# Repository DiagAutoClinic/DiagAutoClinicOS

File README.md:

<!-- HEADER -->

<h1 align="center">DiagAuto Suite</h1>
<h3 align="center">Intelligent CAN Diagnostics &amp; Analysis Platform</h3>

<p align="center">
  <strong>Focused • Hardware-Agnostic • Workshop-Grade</strong><br/>
  Built to analyze, understand, and validate vehicle CAN systems with precision.
</p>

---

# Sponsors / Support (most important)

**DiagAutoClinicOS is currently self-funded by the maintainer (Shaun Smit) and is actively seeking sponsors.**

If this project saves you time or helps your workshop, please consider supporting its development.

> **Support via PayPal → https://paypal.me/diagautoclinic**

Funding options are also listed in `.github/FUNDING.yml`.

---

## Hardware Validation

**Validated on:**
- Godiag GD101 J2534 device
- 500kbps CAN timing with microsecond precision
- ISO-TP fragmentation (FF/CF/FC with BS/STmin)
- Sub-100ms security access (0x27 service)
- USB hotplug recovery with auto-reconnect
- Concurrent session isolation (8 sessions)

**Test vehicles:** Pre-2010 vehicles (per safety protocol)

---

## In-Kind Support / Thanks

The following organizations have provided hardware or resources used during development and testing.

| Contributor                             | Contribution                                                                |
| --------------------------------------- | --------------------------------------------------------------------------- |
| **EshuTech Computers**                  | Development laptop (Acer TravelMate G2 Core i7) for DACOS build environment |
| **GoDiag** — https://godiag.com         | GT100 Plus GPT device for ECU and protocol testing                          |
| **ScanTool.net** — https://scantool.net | OBDLink MX+ adapters for compatibility and reliability testing              |

> In-kind support means hardware or resources were made available to assist development.
> It does **not** imply ongoing financial sponsorship or external funding.

---

## Sponsor Policy / Transparency

Sponsor relationships remain transparent and auditable.

- Sponsor support must never override safety boundaries, Restricted Mode policy, or verification gates.
- Sponsor influence over security controls is **not permitted**.
- Security mechanisms remain **fail-closed**.
- Sponsor-provided code or artifacts must be reviewable and testable.
- Sponsor acknowledgements remain visible in this repository.

---

# Overview

**DiagAuto Suite** is the first production component of **DiagAutoClinicOS (DACOS)**.

The current release focuses exclusively on:

- **CAN diagnostics**
- **signal analysis**
- **vehicle communication logging**

ECU flashing, immobilizer operations, and security access tooling are **intentionally excluded** from the AutoDiag alpha scope and are planned separately in the long-term roadmap.

This design choice prioritizes **stability, safety, and workshop reliability**.

---

## Versioning

This repository contains multiple components with different maturity levels.

- **AutoDiag**: diagnostics module (alpha readiness target: `v0.1`)
- **AutoECU**: programming module (alpha readiness target: `v0.1`, safety-gated)
- **AutoKey**: security/IMMO module (planned)

`config.py` currently sets the runtime/build version (example):

```python
APP_VERSION = "3.2.0"
```

---

## Statement

> "My software will fight you harder to not brick an ECU than most tools fight to stop piracy."
> — Shaun Smit

---

# Repository Layout

This tree is kept in sync with the repository root.

```text
DiagAutoClinicOS/
├── .github/                 GitHub configuration (CI, funding, templates)
├── AutoDiag/                CAN diagnostics suite (PyQt6)
├── AutoECU/                 ECU programming module (alpha / safety-gated)
├── AutoKey/                 Key / immobilizer module (planned)
├── assets/                  Images and static assets
├── core/                    Core shared logic
├── data/                    Reference datasets
├── docs/                    Documentation
├── drivers/                 Hardware driver abstraction / J2534 DLL drop-in
├── installers/              Windows installer scripts
├── layout_samples/          UI prototypes / layout concepts
├── live_tests/              Hardware test scripts
├── plans/                   Architecture plans
├── pulls/                   PR planning notes
├── resources/               Application resources
├── scripts/                 Utility scripts
├── shared/                  Shared modules
├── tests/                   Automated tests
├── ui/                      UI components (shared)
├── utils/                   General utilities
├── Windows Test/            Windows-specific testing
├── check_theme.py           Theme verification helper
├── check_vci.py             VCI verification helper
├── config.py                Global configuration
├── dtc_faults_dataset.json  DTC dataset
├── launcher.py              Suite launcher (PyQt6)
├── launch_autodiag.bat      Convenience launcher for AutoDiag
├── requirements.txt         Runtime dependencies
├── requirements-dev.txt     Development dependencies
├── requirements_32bit.txt   32-bit dependency set
├── pytest.ini               Test configuration
└── version_info.txt         Version info
```

---

# Installation

## System Requirements

- Windows 10 / 11 (64-bit)
- Python 3.10+
- Administrator privileges for hardware drivers

## Running from Source

```bash
git clone https://github.com/DiagAutoClinic/DiagAutoClinicOS.git
cd DiagAutoClinicOS
python -m venv venv
venv\\Scripts\\activate
pip install -r requirements.txt
python launcher.py
```

---

# License

This project is licensed under the **GNU General Public License v3.0**.

---

# Author

**Shaun Smit**  
Founder & Lead Engineer — DiagAutoClinic  
[shaun@diagautoclinic.co.za](mailto:shaun@diagautoclinic.co.za)

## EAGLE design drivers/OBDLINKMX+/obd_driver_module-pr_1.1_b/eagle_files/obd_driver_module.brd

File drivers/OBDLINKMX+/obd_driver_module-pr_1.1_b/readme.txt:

*********************************************************************
   OBD Driver Module, Rev 1.1/B
   Copyright (C) 2013 OBD Solutions, All Rights Reserved
*********************************************************************

======================================
============== Contents ==============
======================================

   eagle_files			Contains the EAGLE source files
   assy.gbr			Top assembly drawing (Gerber RS-274X)
   bom.xls			Bill of materials
   mount.mnt			SMD centroid file (XYRS)
   obd_driver_module.pdf	PDF of the schematic
   pcb.zip			Main PCB production files
   readme.txt			This file

======================================
=============== Notes ================
======================================

 - The gerber files provided are viewed from the top side.
 - Hole sizes are the finished hole sizes.
 - Excellon Format: 1.4 Leading, Absolute, Imperial
 - The board should be routed to the outline in fab.gbr

======================================
========= Revision History ===========
======================================

Rev 1.0	- David D (2012.10.27)
	  Initial release

Rev 1.1 - Jason (2013.09.17)
	  Connected all VOUT pins of regulator,reversed ISO comparator inputs
	  Updated PCB Rev to B

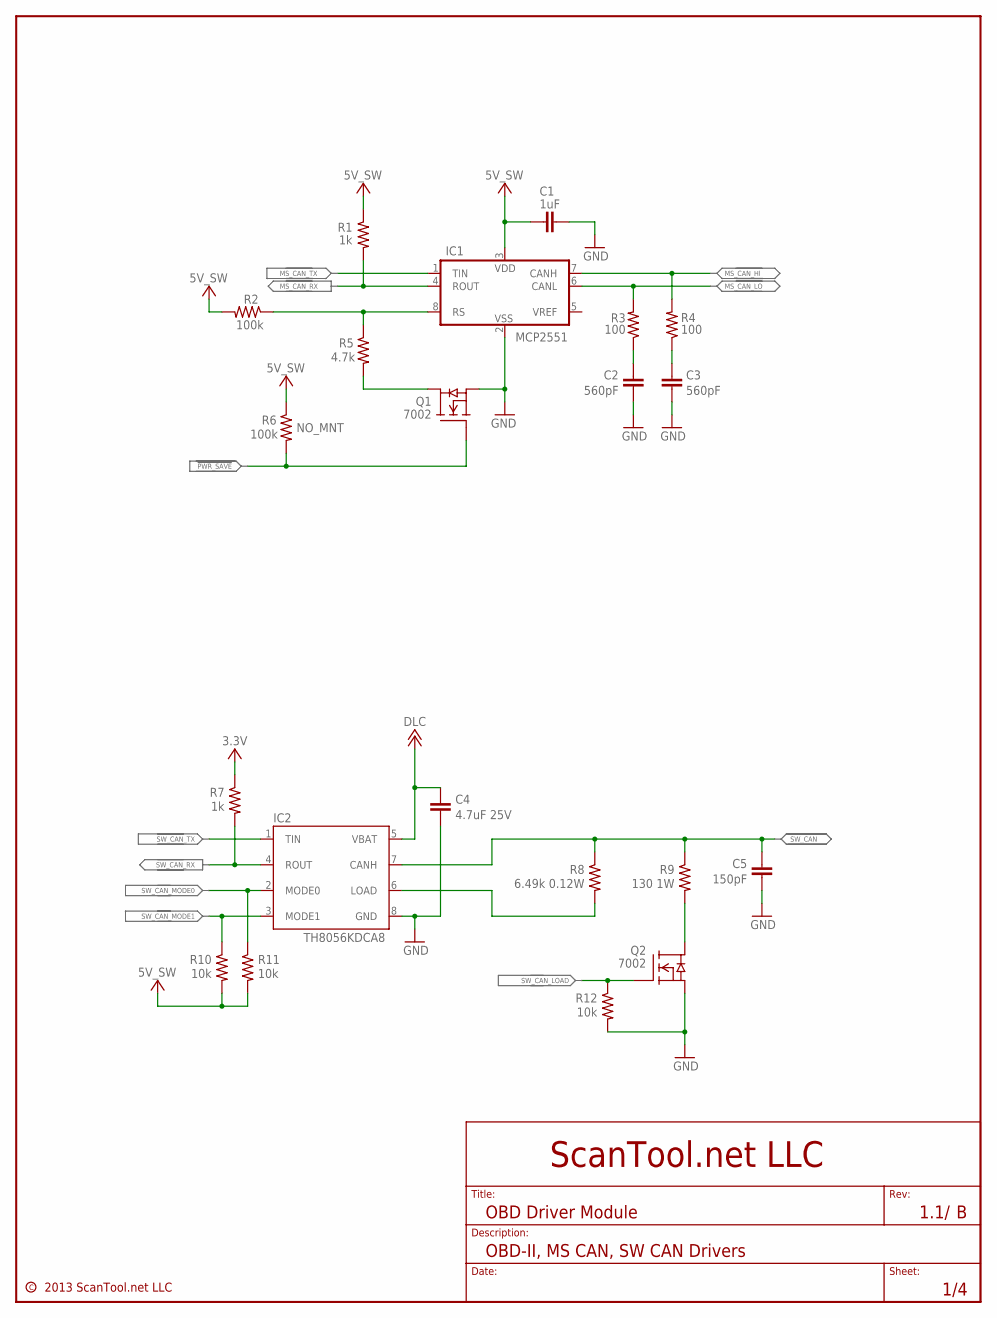
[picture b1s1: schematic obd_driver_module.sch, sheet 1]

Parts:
C1: 1uF; 0603
C2, C3: 560pF; 0603
C4: 4.7uF 25V; 0805
C5: 150pF; 0603
IC1: MCP2551; SO-8
IC2: TH8056KDCA8; SO-8
Q1, Q2: 7002; SOT323-3; PARTNUM 2N7002WT1G
R1, R7: 1k; 0603
R2, R6: 100k; 0603
R3, R4: 100; 0603
R5: 4.7k; 0603
R8: 6.49k 0.12W; 0603
R9: 130 1W; 2512
R10, R11, R12: 10k; 0603

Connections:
3.3V: R7.1; also elsewhere on the board
5V_SW: C1.1, IC1.3 (VDD), R1.1, R2.2, R6.1, R10.2, R11.2; also elsewhere on the board
!PWR_SAVE: Q1.1 (G), R6.2; also elsewhere on the board
DLC: C4.2, IC2.5 (VBAT); also elsewhere on the board
GND: C1.2, C2.2, C3.2, C4.1, C5.1, IC1.2 (VSS), IC2.8 (GND), Q1.2 (S), Q2.2 (S), R12.2; also elsewhere on the board
MS_CAN_HI: IC1.7 (CANH), R4.2; also elsewhere on the board
MS_CAN_LO: IC1.6 (CANL), R3.2; also elsewhere on the board
MS_CAN_RX: IC1.4 (ROUT), R1.2; also elsewhere on the board
MS_CAN_TX: IC1.1 (TIN); also elsewhere on the board
unnamed: C2.1, R3.1
unnamed: C3.1, R4.1
unnamed: IC1.8 (RS), R2.1, R5.1
unnamed: Q1.3 (D), R5.2
unnamed: IC2.6 (LOAD), R8.2
unnamed: Q2.3 (D), R9.P$2 (2)
SW_CAN: C5.2, IC2.7 (CANH), R8.1, R9.P$1 (1); also elsewhere on the board
SW_CAN_LOAD: Q2.1 (G), R12.1; also elsewhere on the board
SW_CAN_MODE0: IC2.2 (MODE0), R11.1; also elsewhere on the board
SW_CAN_MODE1: IC2.3 (MODE1), R10.1; also elsewhere on the board
SW_CAN_RX: IC2.4 (ROUT), R7.2; also elsewhere on the board
SW_CAN_TX: IC2.1 (TIN); also elsewhere on the board

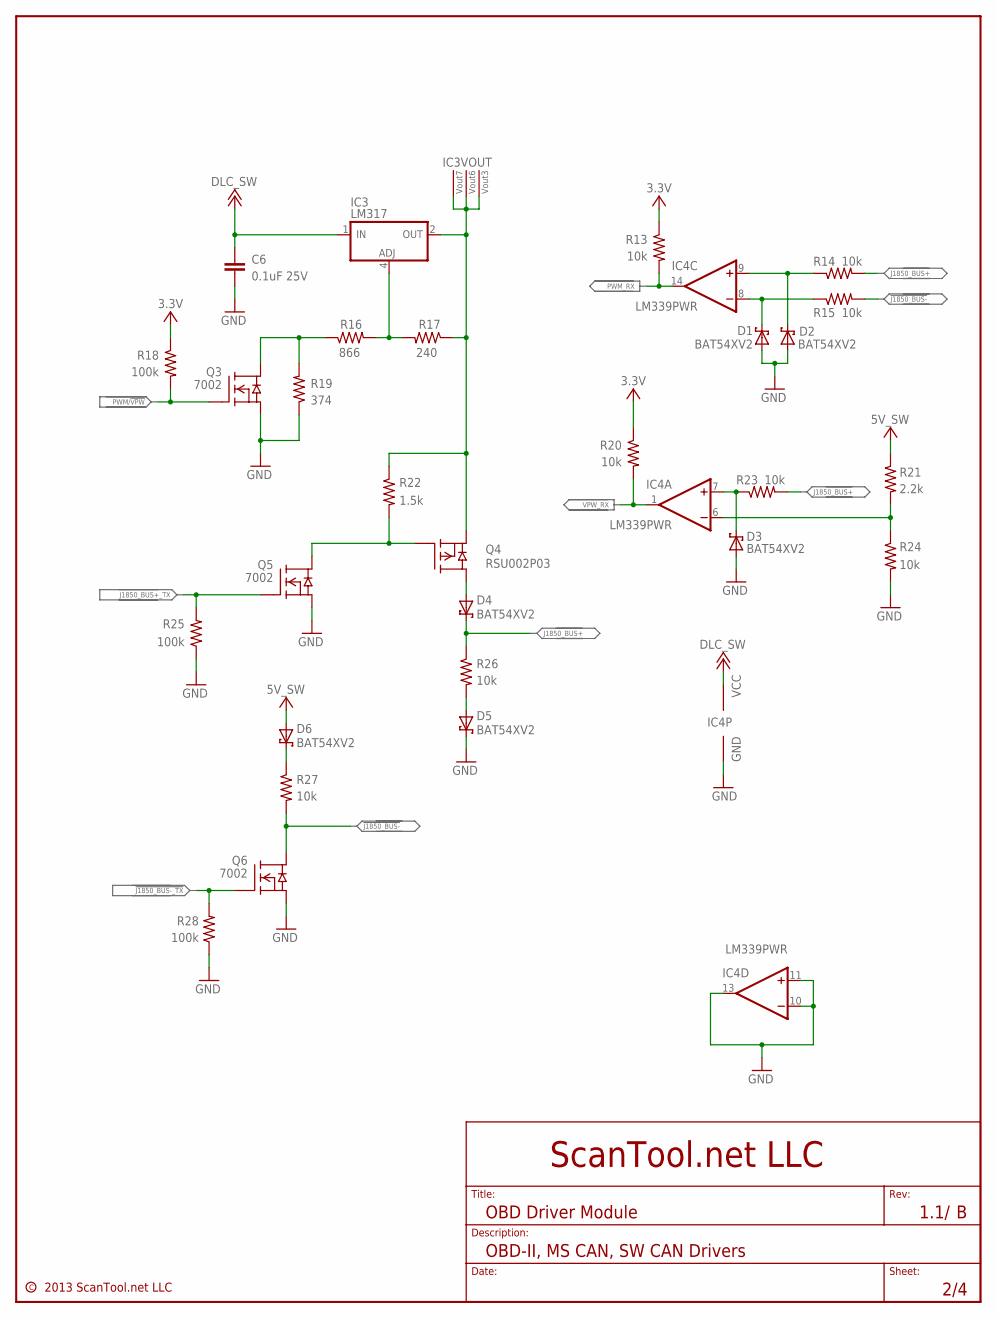
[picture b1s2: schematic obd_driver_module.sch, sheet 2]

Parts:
C6: 0.1uF 25V; 0603
D1, D2, D3: BAT54XV2; SOD-523F; PARTNUM BAT54XV2
D4, D5, D6: BAT54XV2; SOD-523F
IC3: LM317; TSSOP-8
IC4: LM339PWR; TSSOP-14
Q3, Q5, Q6: 7002; SOT323-3; PARTNUM 2N7002WT1G
Q4: RSU002P03; SOT323-3
R13, R14, R15, R20, R23, R24, R26, R27: 10k; 0603
R16: 866; 0603
R17: 240; 0603
R18, R25, R28: 100k; 0603
R19: 374; 0603
R21: 2.2k; 0603
R22: 1.5k; 0603

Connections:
3.3V: R13.1, R18.1, R20.1; also elsewhere on the board
5V_SW: D6.A, R21.1; also elsewhere on the board
!J1850_BUS-: Q6.3 (D), R15.2, R27.2; also elsewhere on the board
!J1850_BUS-_TX: Q6.1 (G), R28.2; also elsewhere on the board
DLC_SW: C6.1, IC3.1 (IN), IC4.3 (VCC); also elsewhere on the board
GND: C6.2, D1.A, D2.A, D3.A, D5.C, IC4.10 (-IN), IC4.11 (+IN), IC4.12 (GND), IC4.13 (OUT), Q3.2 (S), Q5.2 (S), Q6.2 (S), R19.1, R24.2, R25.1, R28.1; also elsewhere on the board
J1850_BUS+: D4.C, R14.2, R23.2, R26.1; also elsewhere on the board
J1850_BUS+_TX: Q5.1 (G), R25.2; also elsewhere on the board
unnamed: D6.C, R27.1
unnamed: Q4.1 (G), Q5.3 (D), R22.2
unnamed: Q3.3 (D), R16.1, R19.2
unnamed: D3.C, IC4.7 (+IN), R23.1
unnamed: D5.A, R26.2
unnamed: IC3.4 (ADJ), R16.2, R17.2
unnamed: D4.A, Q4.3 (D)
unnamed: D2.C, IC4.9 (+IN), R14.1
unnamed: D1.C, IC4.8 (-IN), R15.1
unnamed: IC4.6 (-IN), R21.2, R24.1
OUT: IC3.2 (OUT), IC3.3 (OUT), IC3.6 (OUT), IC3.7 (OUT), Q4.2 (S), R17.1, R22.1
PWM/!VPW: Q3.1 (G), R18.2; also elsewhere on the board
PWM_RX: IC4.14 (OUT), R13.2; also elsewhere on the board
VPW_RX: IC4.1 (OUT), R20.2; also elsewhere on the board

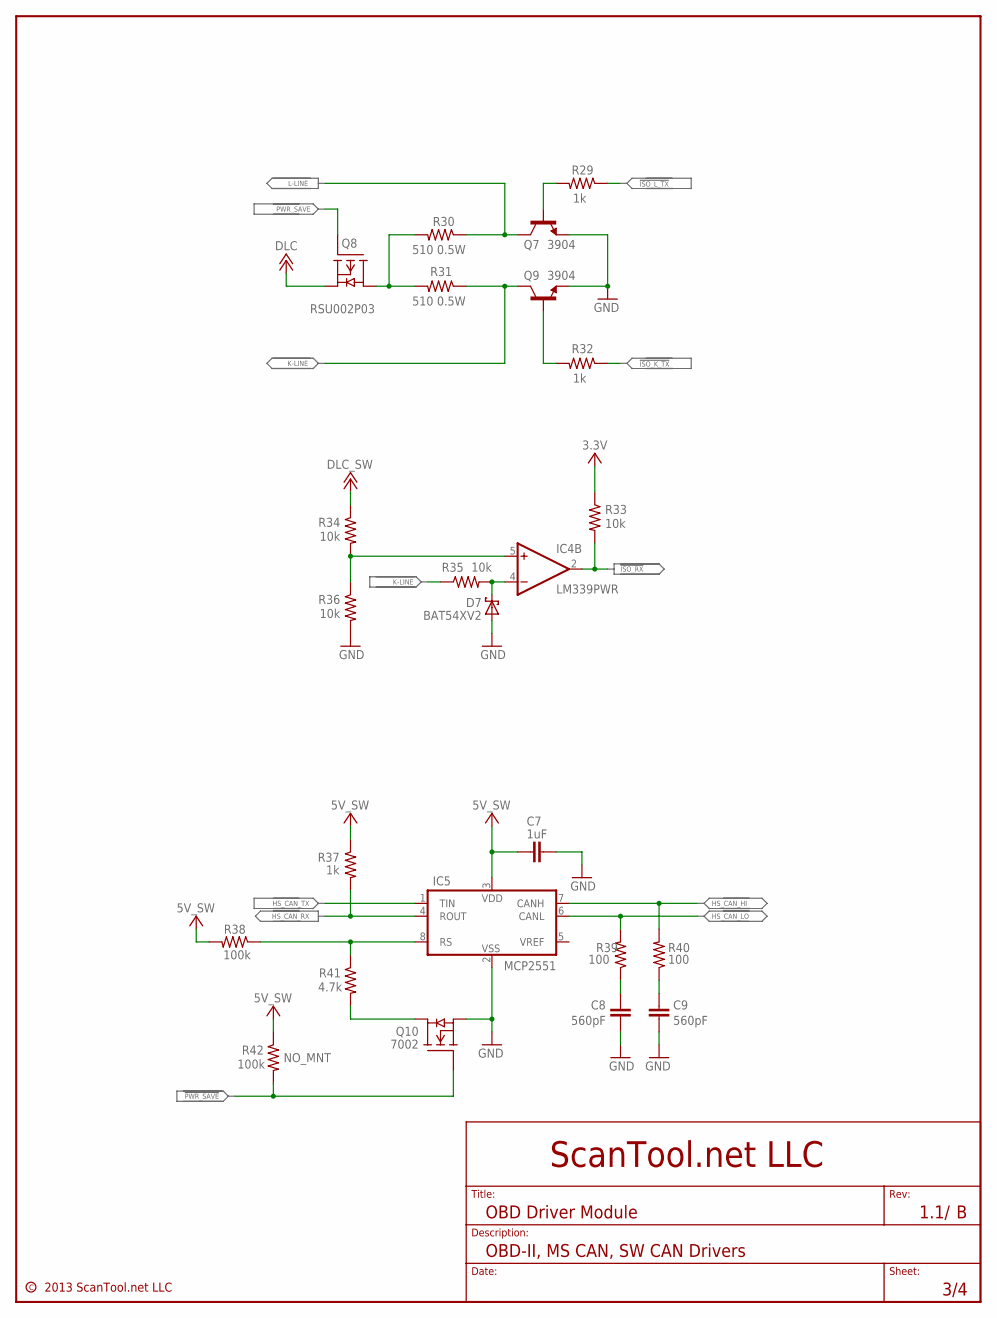
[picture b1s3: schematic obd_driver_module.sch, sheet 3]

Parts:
C7: 1uF; 0603
C8, C9: 560pF; 0603
D7: BAT54XV2; SOD-523F
IC4: LM339PWR; TSSOP-14
IC5: MCP2551; SO-8
Q7, Q9: 3904; SOT323-3
Q8: RSU002P03; SOT323-3
Q10: 7002; SOT323-3; PARTNUM 2N7002WT1G
R29, R32, R37: 1k; 0603
R30, R31: 510 0.5W; 1210
R33, R34, R35, R36: 10k; 0603
R38, R42: 100k; 0603
R39, R40: 100; 0603
R41: 4.7k; 0603

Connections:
3.3V: R33.1; also elsewhere on the board
5V_SW: C7.1, IC5.3 (VDD), R37.1, R38.2, R42.1; also elsewhere on the board
!ISO_K_TX: R32.1; also elsewhere on the board
!ISO_L_TX: R29.1; also elsewhere on the board
!ISO_RX: IC4.2 (OUT), R33.2; also elsewhere on the board
!PWR_SAVE: Q10.1 (G), R42.2; also elsewhere on the board
DLC: Q8.2 (S); also elsewhere on the board
DLC_SW: R34.1; also elsewhere on the board
GND: C7.2, C8.2, C9.2, D7.A, IC5.2 (VSS), Q7.2 (E), Q9.2 (E), Q10.2 (S), R36.2; also elsewhere on the board
HS_CAN_HI: IC5.7 (CANH), R40.2; also elsewhere on the board
HS_CAN_LO: IC5.6 (CANL), R39.2; also elsewhere on the board
HS_CAN_RX: IC5.4 (ROUT), R37.2; also elsewhere on the board
HS_CAN_TX: IC5.1 (TIN); also elsewhere on the board
K-LINE: Q9.3 (C), R31.1, R35.1; also elsewhere on the board
L-LINE: Q7.3 (C), R30.1; also elsewhere on the board
unnamed: C8.1, R39.1
unnamed: Q10.3 (D), R41.2
unnamed: Q7.1 (B), R29.2
unnamed: Q8.3 (D), R30.2, R31.2
unnamed: Q9.1 (B), R32.2
unnamed: D7.C, IC4.4 (-IN), R35.2
unnamed: IC5.8 (RS), R38.1, R41.1
unnamed: IC4.5 (+IN), R34.2, R36.1
unnamed: C9.1, R40.1
PWR_SAVE: Q8.1 (G); also elsewhere on the board

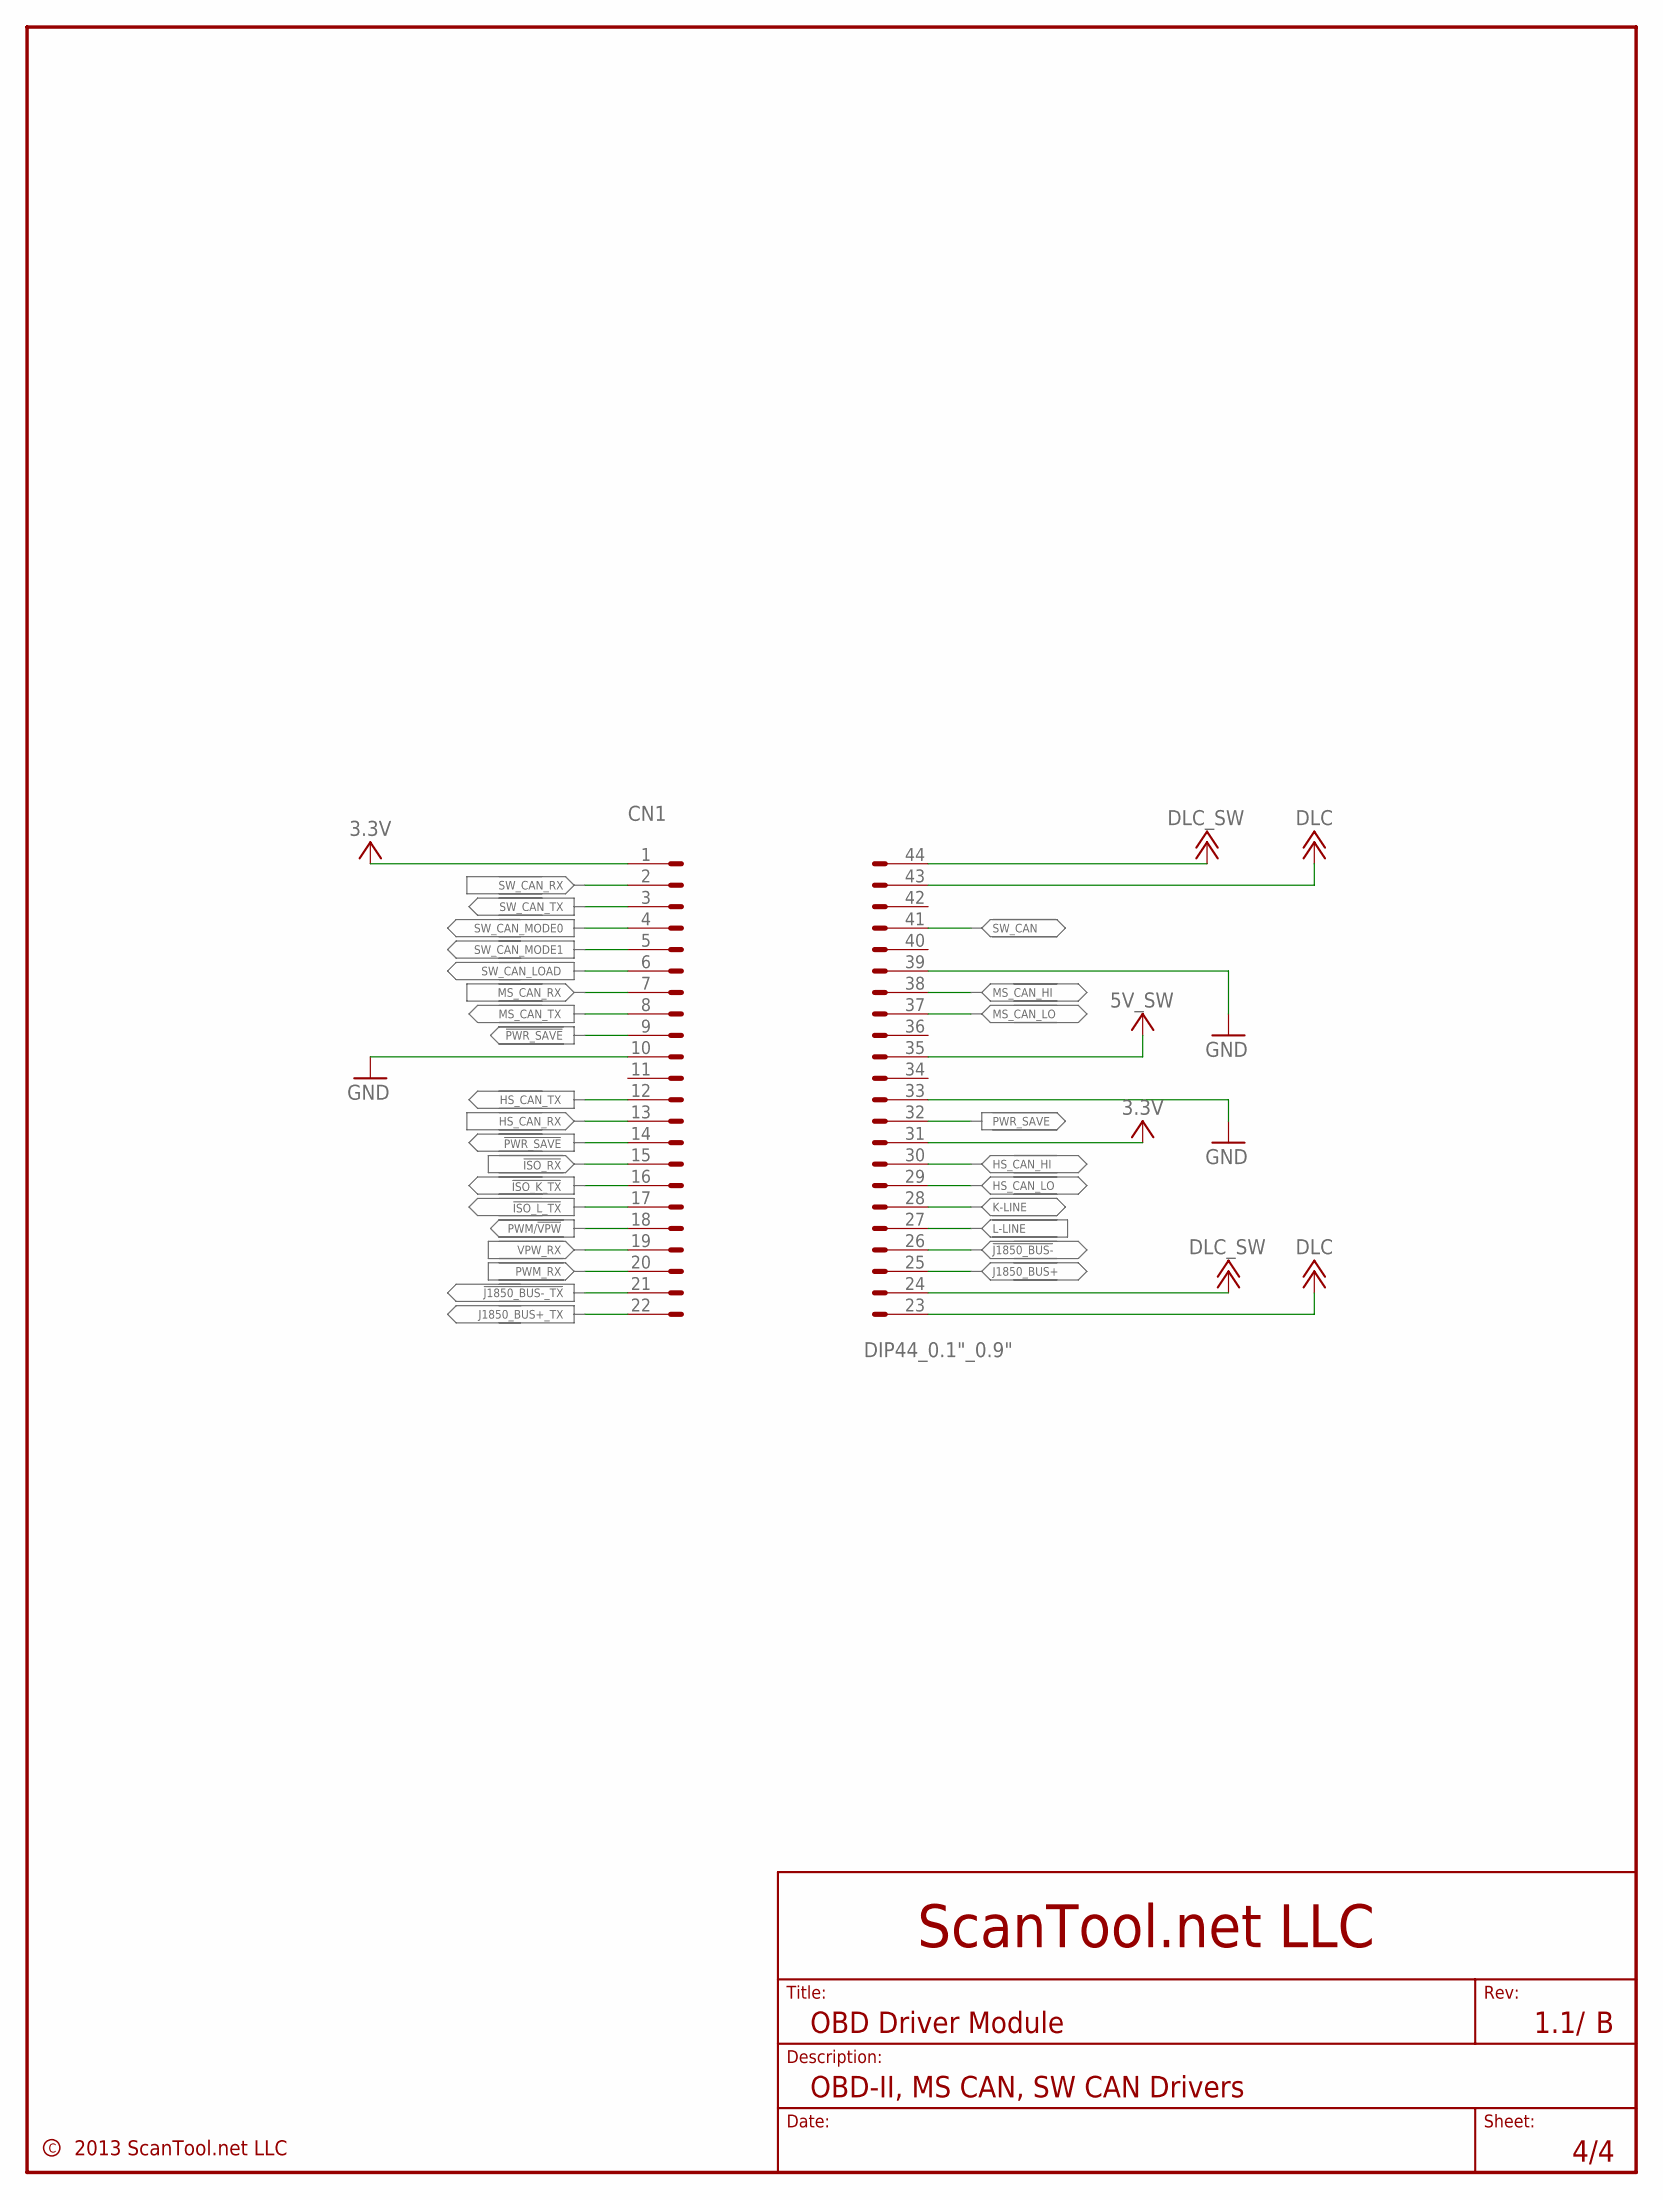
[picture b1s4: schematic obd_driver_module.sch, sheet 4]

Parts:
CN1: DIP44_0.1"_0.9"

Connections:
3.3V: CN1.1, CN1.31; also elsewhere on the board
5V_SW: CN1.35; also elsewhere on the board
!ISO_K_TX: CN1.16; also elsewhere on the board
!ISO_L_TX: CN1.17; also elsewhere on the board
!ISO_RX: CN1.15; also elsewhere on the board
!J1850_BUS-: CN1.26; also elsewhere on the board
!J1850_BUS-_TX: CN1.21; also elsewhere on the board
!PWR_SAVE: CN1.9, CN1.14; also elsewhere on the board
DLC: CN1.23, CN1.43; also elsewhere on the board
DLC_SW: CN1.24, CN1.44; also elsewhere on the board
GND: CN1.10, CN1.33, CN1.39; also elsewhere on the board
HS_CAN_HI: CN1.30; also elsewhere on the board
HS_CAN_LO: CN1.29; also elsewhere on the board
HS_CAN_RX: CN1.13; also elsewhere on the board
HS_CAN_TX: CN1.12; also elsewhere on the board
J1850_BUS+: CN1.25; also elsewhere on the board
J1850_BUS+_TX: CN1.22; also elsewhere on the board
K-LINE: CN1.28; also elsewhere on the board
L-LINE: CN1.27; also elsewhere on the board
MS_CAN_HI: CN1.38; also elsewhere on the board
MS_CAN_LO: CN1.37; also elsewhere on the board
MS_CAN_RX: CN1.7; also elsewhere on the board
MS_CAN_TX: CN1.8; also elsewhere on the board
PWM/!VPW: CN1.18; also elsewhere on the board
PWM_RX: CN1.20; also elsewhere on the board
PWR_SAVE: CN1.32; also elsewhere on the board
SW_CAN: CN1.41; also elsewhere on the board
SW_CAN_LOAD: CN1.6; also elsewhere on the board
SW_CAN_MODE0: CN1.4; also elsewhere on the board
SW_CAN_MODE1: CN1.5; also elsewhere on the board
SW_CAN_RX: CN1.2; also elsewhere on the board
SW_CAN_TX: CN1.3; also elsewhere on the board
VPW_RX: CN1.19; also elsewhere on the board

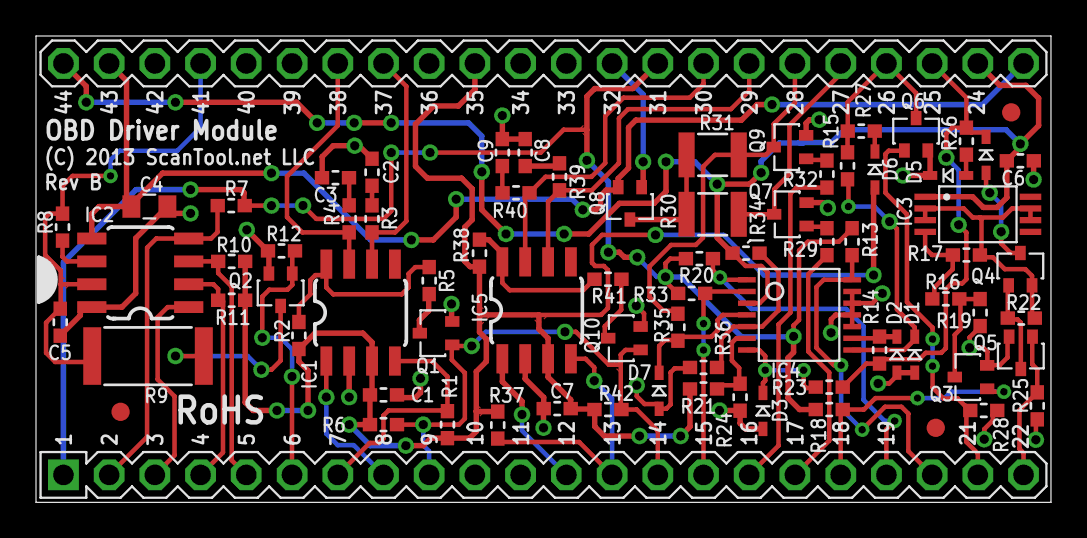
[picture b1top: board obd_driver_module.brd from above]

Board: 2 copper layers, 56.4 x 25.9 mm, 77 parts (0 on the bottom side), 59 nets.

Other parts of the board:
E$4, E$5, E$6: FIDUCIAL_40X100

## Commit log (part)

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2025-10-04 Create 1
2025-10-04 Create iso
2025-10-07 🚀 DiagAutoClinicOS v2.0 - Professional Vehicle Diagnostic Suite
    - Complete professional-grade automotive software
    - AutoDiag, AutoECU, and AutoKey applications
    - Shared modules for hardware abstraction
    - Bluetooth integration scripts
    - Professional PyQt6 interface
    - Build system and installation setup
2025-10-09 Create update_windows_req.py
    Added Windows option for testing
2025-10-09 Create install_windows.py
    Windows Test Installation
2025-10-09 Update launcher.py
    Patched by Grok
2025-10-09 Update device_handler.py
    Patched by Grok
2025-10-09 Update main.py
    Patched by Grok
2025-10-09 Update main.py
    Full fledged sys testable Linux
2025-10-10 Create main_v2_beta.py
    Functional, secured and 25 Brands added stiill testing to be done.
2025-10-10 Create special_functions.py
    Special Functions Module skeleton
2025-10-10 Create Calabrations_reset.py
    Calabration & reset Module skeleton
2025-10-10 Create intergration_autodiag.py
    Intergration of AutoDiag Suite Modules
2025-10-10 Create security_manager.py
    Security Manager Skeleton
2025-10-10 Create enhanced_intergration.py
    Enhanced Intergration for AutoDiag
2025-10-10 Create enhanced_style_manager.py
    Enhancememt for style
2025-10-10 Create FUNDING.yml
    PayPal link added
2025-10-11 Rename shared/Calabrations_reset.py to calibrations_reset.py
    Correct file typo's
2025-10-11 Rename shared/enhanced_intergration.py to enhanced_integration.py
    Correct file typo's
2025-10-11 Rename shared/intergration_autodiag.py to integration_autodiag.py
    Correct file typo's
2025-10-11 Update main_v2_beta.py
    Correct file typo's
2025-10-11 Rename calibrations_reset.py to shared/calibrations_reset.py
    Moved to shared
2025-10-11 Rename enhanced_integration.py to shared/enhanced_integration.py
    Moved to shared
2025-10-11 Rename integration_autodiag.py to shared/integration_autodiag.py
    Moved to shared
2025-10-11 Update security_manager.py
    Enhanced Security manager
2025-10-11 Update style_manager.py
    Enhanced
2025-10-11 Update main_v2_beta.py
    Enhanced
2025-10-11 Update brand_database.py
    Complete 25 brands
2025-10-19 Create __init__.py
    Create test phase file struckture for AutoDiag Suite
2025-10-19 Create conftest.py
    File struckture
2025-10-19 Delete tests/AutoDiag/functional/test_full_diagnostic.py
    Named wrong
2025-10-31 Add futuristic glassmorphic theme to style manager
    Updated the Enhanced Style Manager to include a new futuristic glassmorphic theme. Adjusted theme settings, added new theme methods, and modified stylesheet definitions for a modern look.
2025-10-31 Add Circular Gauge and StatCard widgets
    This file implements a Circular Gauge widget for modern data visualization, including a StatCard that utilizes the gauge.
2025-10-31 Revamp launcher to modern futuristic design and features
    Updated the launcher for DiagAutoClinicOS to version 3.0 with a modern glassmorphic design, improved UI elements, and enhanced functionality.
2025-11-01 Update print statement from 'Hello' to 'Goodbye'
2025-11-01 Revamp UI to futuristic design with teal theme
    Updated the AutoECU application to feature a futuristic glassmorphic design with a teal theme. Enhanced UI components, added fallback classes for style management, and improved functionality for ECU 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
2025-11-01 Revamp UI to Futuristic Design with Enhanced Features
    Updated application branding and user interface to reflect a futuristic design with improved theme support and additional components.
2025-11-06 update project files
2025-11-10 feat(DACOS): complete offline rebuild - AutoECU glassmorphic UI + all modules updated
    - Fixed style_manager across entire project
    - Futuristic Teal theme with live glow effects
    - AutoDiag/AutoECU/AutoKey all synced
    - Added pro device integration tests
    - launcher.py ready for AppImage
    - Removed local AI script from repo (security)
2025-11-10 HARDENED: full offline rebuild + new SSH keys Nov 10 2025 (old laptop nuked)
2025-11-10 Refactor UI elements and improve layout
    Updated various labels and button texts to remove emojis for a cleaner interface. Adjusted the style manager import and initialization. Increased window size for better layout.
2025-11-10 Some interesting changes done
2025-11-10 Revise README for improved clarity and organization
    Updated README.md to enhance structure, branding, and content clarity.
2025-11-11 Revise README for clarity and structure
    Updated README.md to enhance clarity and organization, including theme options, hardware support, and acknowledgments.
2025-11-11 Revise acknowledgments and team description in README
    Updated acknowledgments and team name in README.
2025-11-11 Format sponsor section in README.md
2025-11-11 Revise README for better organization and content
    Updated README.md for improved clarity and structure.
2025-11-11 Update README with new sponsor logos and cleanup
    Removed duplicate images and updated sponsor logos.
2025-11-11 Fix duplicate sponsor image in README
    Removed duplicate sponsor image section in README.
2025-11-11 Correct HTML tags in sponsors section
    Fix HTML formatting for sponsors section in README.
2025-11-11 Fix HTML encoding issues in README.md
2025-11-11 Fix HTML formatting in README.md
2025-11-11 Fix README formatting and update sponsor image link
2025-11-11 Refactor sponsor section in README.md
    Updated HTML structure for sponsor section in README.
2025-11-11 Enhance sponsor display in README
    Updated sponsor section with improved formatting and alignment.
2025-11-11 Format contact information for integration testing
    Updated contact information format for integration testing inquiries.
2025-11-13 SSH fully working + latest code
2025-11-13 Update error fixing
2025-11-15 feat: VW Polo/Golf live testing enhancements
2025-11-15 docs: Revamp README.md with VW Polo/Golf focus and collaborator recognition
2025-11-15 Backup commit before continuing tomorrow - test failed due to missing PyQt6
2025-11-15 Fix import issues: add PYTHONPATH to launcher, fix fallback style managers, correct imports for Protocol and SpecialFunction
2025-11-21 Backup commit - All current work ready for tonight
2025-11-21 Update AutoDiag, AutoECU, and AutoKey modules with enhanced styling and UI improvements
2025-11-23 Add auto-approve config to .gitignore and update project files
2025-11-23 Update main modules, requirements, and add development dependencies summary
2025-11-24 Update AutoDiag main, README, and login dialog with improvements
2025-11-24 Add neural background functionality and enhance core modules
2025-11-27 Add mock data for Advanced tab in AutoDiag using shared/advance.py
2025-11-30 Finalize GUI implementation and initiate live testing phase
2025-11-30 Remove VW testing files and shift focus to Ford/GM
2025-11-30 Update README.md with v3.1.0 VW Polo/Golf release information
2025-11-30 Correct README.md to focus on Ford Ranger and Figo, remove VW references
2025-11-30 Add Ford CAN bus sniffer files: can_sniff_obdlink.py and capture logs for Figo and Ranger
2025-11-30 Remove sniffer files from repository - internal use only
2025-12-01 Add December 1, 2025 comprehensive testing results: 6 hardware integrations successful, 552 CAN messages captured, dual-device workflows operational, production ready status achieved
2025-12-01 Add initial content to 1.py
2025-12-04 Comprehensive update: AI implementation, Land Rover calibration, CAN bus data, and test suite
2025-12-07 Backup commit before creating backup on D:\DACOS"
2025-12-12 Revise README for global context and inclusivity
    Updated documentation to reflect a global focus instead of just South African conditions.
2025-12-13 feat: Professional Windows Installer v3.2.0 with SQL Server Express integration
2025-12-16 Add installer setup, documentation, and validation scripts
2025-12-16 Remove large binaries and update .gitignore to exclude them
2025-12-16 Update README.md for v3.2.0: Add Windows installer section, validation results, and Afrikaans support
2025-12-16 Update README with SQLite CAN database info and latest testing achievements
2025-12-18 Revise README for v3.1.0 release details
    Updated the README to reflect the latest version and features of DiagAuto Suite, including installation instructions, project vision, and acknowledgements.
2025-12-19 Staged changes
2025-12-20 Update project files with new features, tests, and documentation
2025-12-20 Exclude .venv from git and remove unrelated website files
2025-12-24 Update project files and add new features
2025-12-28 Update README with performance optimization achievements and add comprehensive performance monitoring system
2026-01-02 Update project with latest changes
2026-01-02 Change logo URL in README.md
    Updated logo URL in README file.
2026-01-09 Revise README for logo and feature updates
    Updated the README to reflect changes in logo, features, installation instructions, and performance optimizations.
2026-01-09 Update .gitignore to exclude AI, venv, and test files; add new features and docs
2026-01-09 Migrate exe files to Git LFS and add new features
2026-01-14 Update project files and exclude AI agent components
2026-01-14 docs: sponsor transparency and local dev notes
2026-01-14 chore: keep tests and security artifacts local
2026-01-14 docs: clarify local-only artifacts; ignore local datasets
2026-01-14 chore: remove local training dataset from repo
2026-02-22 Initial plan
2026-02-22 Fix AutoDiag and integrate C/C++ where needed for release
2026-02-26 Update funding options
2026-02-26 Stabilize AutoDiag startup and add native J2534 C++ probe
2026-03-01 Revamp README.md: sponsors section, repo layout, fix duplicate sections and clone URL
2026-03-01 Add login gating, HWID tracking, fix launcher bugs, add smoke tests
2026-03-01 Add tests directory and update .gitignore to track tests/
2026-03-01 Marking pull request #4 as ready for review
2026-03-07 Update .gitignore with additional exclusions
    Expanded .gitignore to include various build artifacts, IDE files, OS artifacts, security files, and AI training data.
2026-03-07 Modify .gitignore for new test and config entries
    Updated .gitignore to include new entries for live tests, Windows Test, and to uncomment the PDF exclusion.
2026-03-07 Refactor README.md for clarity and formatting
    Updated README.md to enhance formatting, clarify sections, and improve overall readability. Adjusted headings, added emphasis on key features, and refined installation instructions.
2026-03-07 Document Copilot core rules and engineering principles
    Added core rules and guidelines for Copilot usage in the repository, including scope boundaries, version model, and engineering principles.
2026-03-08 Add pytest configuration for test discovery
2026-03-12 feat(AutoECU): implement Truth System Phase 1 – state machine, truth gate, file integrity, JSONL audit log + 68 unit tests
2026-04-12 Update README.md with new content
2026-04-14 Restrict main execution to launcher.py only
2026-05-02 fix(launcher): clean up unused imports, fix QT_QPA_PLATFORM for cross-platform, remove dead code
    Agent-Logs-Url: https://github.com/DiagAutoClinic/DiagAutoClinicOS/sessions/2147f63e-bb48-4912-a071-ca8309b912e6

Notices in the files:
drivers/OBDLINKMX+/obd_driver_module-pr_1.1_b/eagle_files/obd_driver_module.brd:
(C) 2013 ScanTool.net LLC
